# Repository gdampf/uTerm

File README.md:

## uTerm

uTerm (micro-Term) is a VT100-like terminal for the Z80-MBC2 (https://hackaday.io/project/159973). It has a VGA out and PS/2 keyboard connector, a power supply for the Z80-MBC2 and a "transparent" serial-USB port.

This fork of https://github.com/SuperFabius/uTerm was originally made for supporting German Keyboard-Layout.
Then, I recognized, that some kind of keyboards with PS/2 doesn't react at the given firmware. They are just sending out 0xAA all the time and no key codes. By comparing the signals to a system, where they are working fine, I found that they need a reset (0xff), to work propperly.
This fork solve therefore three things:

1. the state machine for the keyboard has been changed to support this kind of keyboards, which are waiting for reset.
2. the right alt key is now used as a separate modifier to support the ALTGR-Codes on many non US-Keyboard-Layouts.
3. the keys are changed corresponding to German Layout

To compile this code, I used Keil µVision5 under Windows X!

I further added the code for using an ESP8266 for using telnet via WiFi.

Here comes the original Text:

These are the sources modified for the uTerm forked from the Madis Kaal 
repository (forked from the original repository of K. C. Lee: 
https://github.com/FPGA-Computer/STM32F030F4-VGA. Original project 
page: https://hw-by-design.blogspot.com/2018/07/low-cost-vga-terminal-module-project.html)

uTerm "project" page: https://hackaday.io/project/165325

NOTE: I've updated here only the changed source files, so you must recompile all to get the new executable.

Supported uTerm boards:

- A071218-R250119
- A071218-R290319

Supported uTerm-S boards:

- A200419

------------------------------------------------------------------------------

**UPDATE (11/2019):** Solved a bug (by gkaufman) using the right CTRL key in some situations (i.e. CTRL-L)

------------------------------------------------------------------------------

In the following the original text. 

------------------------------------------------------------------------------
------------------------------------------------------------------------------

VT100 emulation, font editor, 16-line font, and support for inverse fonts
added by Madis Kaal <mast@nomad.ee> http://www.nomad.ee

The individual license(s) are in each directories.

Directories:
------------------------------------------------------------------------------
font conv/ 
- source code + Windows console executable for a font conversion program.
It imports GLCD font Creator file and converter it to a C font table
of the comverted scan line bitmaps that is to be used with the VGA library.

- The converter is compiled using Pelles C
http://www.pellesc.de/index.php?page=start&lang=en

- "GLCD Font Creator" MikroElektronika
http://www.mikroe.com/glcd-font-creator/

Code in this directory is licensed under "Simplified BSD License"

-------------------------------------------------------------------------------
STM32F030F4/Hardware/LT Spice Simulation
files in this directory is licensed under "Simplified BSD License"

-------------------------------------------------------------------------------
STM32F030F4/Hardware/Sketchup 3D Model
Creative Commons 4.0 Attribution-NonCommercial-NoDerivs International
http://creativecommons.org/licenses/by-nc-nd/4.0/

This is to prevent someone photoshopping this as their own project for crowd-funding 
scams. You are free to generate your own model using Eagleup from your new layout.

-------------------------------------------------------------------------------
STM32F030F4/Hardware/
Schematic/Layout is distributed with Creative Commons 4.0 Attribution-NonCommercial
http://creativecommons.org/licenses/by-nc/4.0/

If you want to sell this and want a different licensing term, please contact me.

-------------------------------------------------------------------------------
STM32F030F4/Firmware/

Source code distributed under GPLV3, with exception of fontedit.py that is
distributed under BSD license.

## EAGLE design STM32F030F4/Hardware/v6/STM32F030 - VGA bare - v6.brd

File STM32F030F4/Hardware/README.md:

ChibiTerm
---------
This is the repository for the Low Cost VGA Terminal Module PCB.

Licensing:
Schematic/Layout is distributed with Creative Commons 4.0 Attribution-NonCommercial

3D modelling: Creative Commons 4.0 Attribution-NonCommercial-NoDerivs International
This is to prevent someone photoshopping this as their own project for crowd-funding scams. You are allowed to generate your own model using Eagleup from your new layout.

Creative Commons 4.0 Attribution-NonCommercial:
See http://creativecommons.org/licenses/by-nc/4.0/

Creative Commons 4.0 Attribution-NonCommercial-NoDerivatives International
See http://creativecommons.org/licenses/by-nc-nd/4.0/

If you want to sell this and want a different licensing term, please contact me.

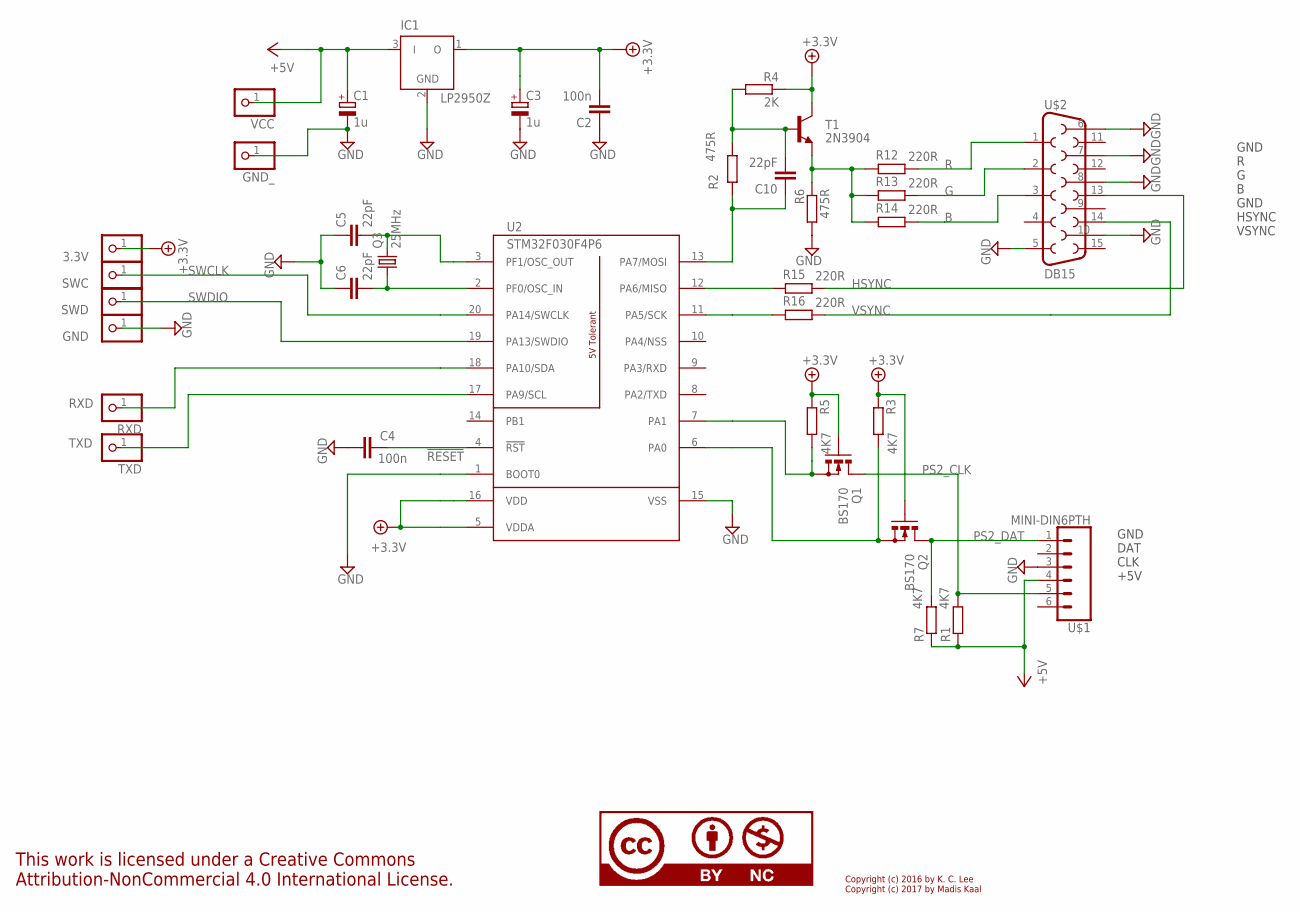
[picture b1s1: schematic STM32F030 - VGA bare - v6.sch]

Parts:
3.3V: PINHD-1X1; 1X01
C1, C3: 1u; E2,5-5
C2, C4: 100n; C025-025X050; PARTNO 0.1UF, 0603
C5, C6, C10: 22pF; C025-025X050; PARTNO 22PF, 0603
GND: PINHD-1X1; 1X01
GND_: PINHD-1X1; 1X01
IC1: LP2950Z; TO92
LICENSE: CC-BY-NC; CC-BY-NC-75; PARTNO LICENSE
Q1, Q2: BS170; SOT54E
Q3: 25MHz; HC49U-V
R1, R3, R5, R7: 4K7; 0204/7; PARTNO 4K7, 0603
R2, R6: 475R; 0204/7; PARTNO 475R, 0603
R4: 2K; 0204/7; PARTNO 2K, 0603
R12, R13, R14, R15, R16: 220R; 0204/7
RXD: PINHD-1X1; 1X01
SWC: PINHD-1X1; 1X01
SWD: PINHD-1X1; 1X01
T1: 2N3904; TO92
TXD: PINHD-1X1; 1X01
U2: STM32F030F4P6; TSSOP20; PARTNO STM32F030F4P6
U$1: MINI-DIN6PTH; MINI-DIN6
U$2: DB15
VCC: PINHD-1X1; 1X01

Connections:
!RESET: C4.1, U2.4 (!RST)
+3.3V: 3.3V.1, C2.2, C3.+, IC1.1 (O), Q1.G, Q2.G, R3.2, R4.1, R5.2, T1.1 (C), U2.5 (VDDA), U2.16 (VDD)
+5V: C1.+, IC1.3 (I), R1.2, R7.2, U$1.4, VCC.1
B: R14.1, U$2.3
G: R13.1, U$2.2
GND: C1.-, C2.1, C3.-, C4.2, C5.1, C6.1, GND.1, GND_.1, IC1.2 (GND), R6.2, U2.1 (BOOT0), U2.15 (VSS), U$1.3, U$2.5, U$2.6, U$2.7, U$2.8, U$2.10
HSYNC: R15.1, U$2.13
unnamed: R6.1, R12.2, R13.2, R14.2, T1.3 (E)
unnamed: R15.2, U2.12 (PA6/MISO)
unnamed: Q1.S, R5.1, U2.7 (PA1)
unnamed: C5.2, Q3.2, U2.3 (PF1/OSC_OUT)
unnamed: C6.2, Q3.1, U2.2 (PF0/OSC_IN)
unnamed: Q2.S, R3.1, U2.6 (PA0)
unnamed: R16.2, U2.11 (PA5/SCK)
unnamed: C10.2, R2.1, R4.2, T1.2 (B)
unnamed: C10.1, R2.2, U2.13 (PA7/MOSI)
PS2_CLK: Q1.D, R1.1, U$1.5
PS2_DAT: Q2.D, R7.1, U$1.1
R: R12.1, U$2.1
RXD: RXD.1, U2.18 (PA10/SDA)
SWCLK: SWC.1, U2.20 (PA14/SWCLK)
SWDIO: SWD.1, U2.19 (PA13/SWDIO)
TXD: TXD.1, U2.17 (PA9/SCL)
VSYNC: R16.1, U$2.14

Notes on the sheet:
GND R G B GND HSYNC VSYNC
GND DAT CLK +5V
Copyright (c) 2016 by K. C. Lee Copyright (c) 2017 by Madis Kaal

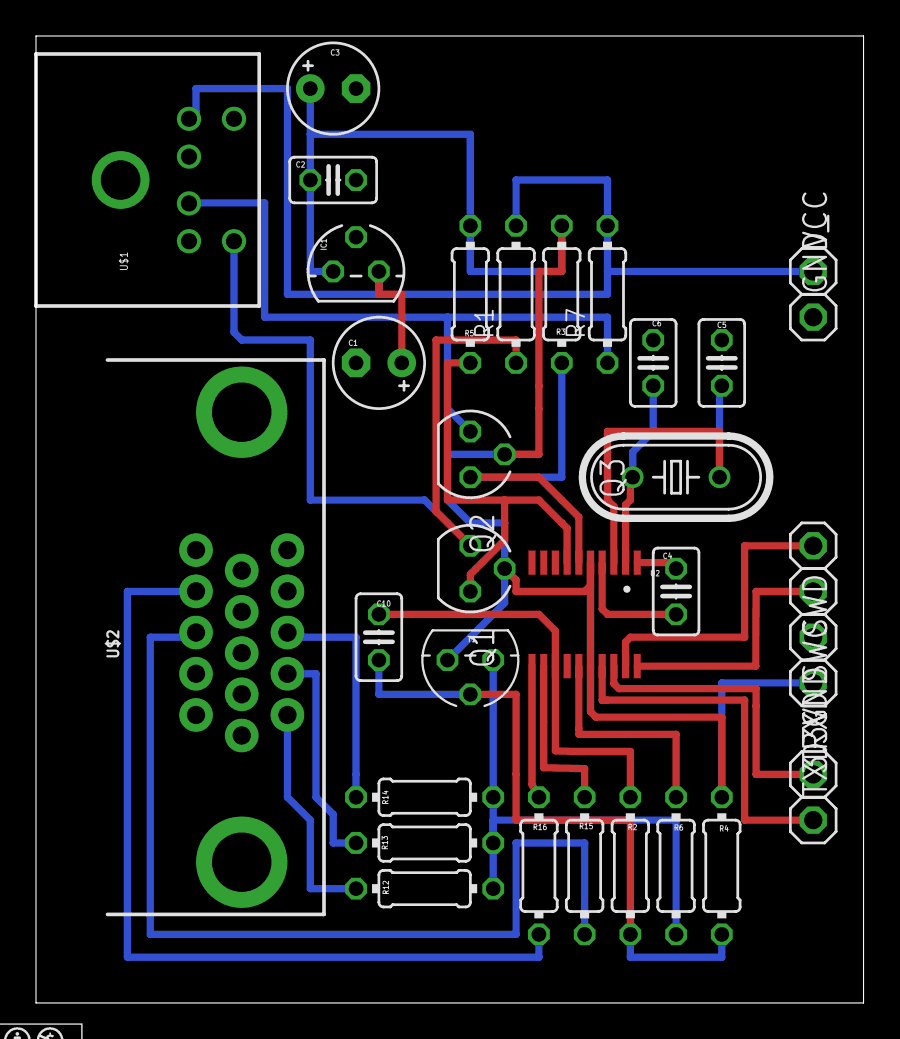
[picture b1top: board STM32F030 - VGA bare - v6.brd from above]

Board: 2 copper layers, 46.0 x 53.7 mm, 36 parts (0 on the bottom side), 24 nets.

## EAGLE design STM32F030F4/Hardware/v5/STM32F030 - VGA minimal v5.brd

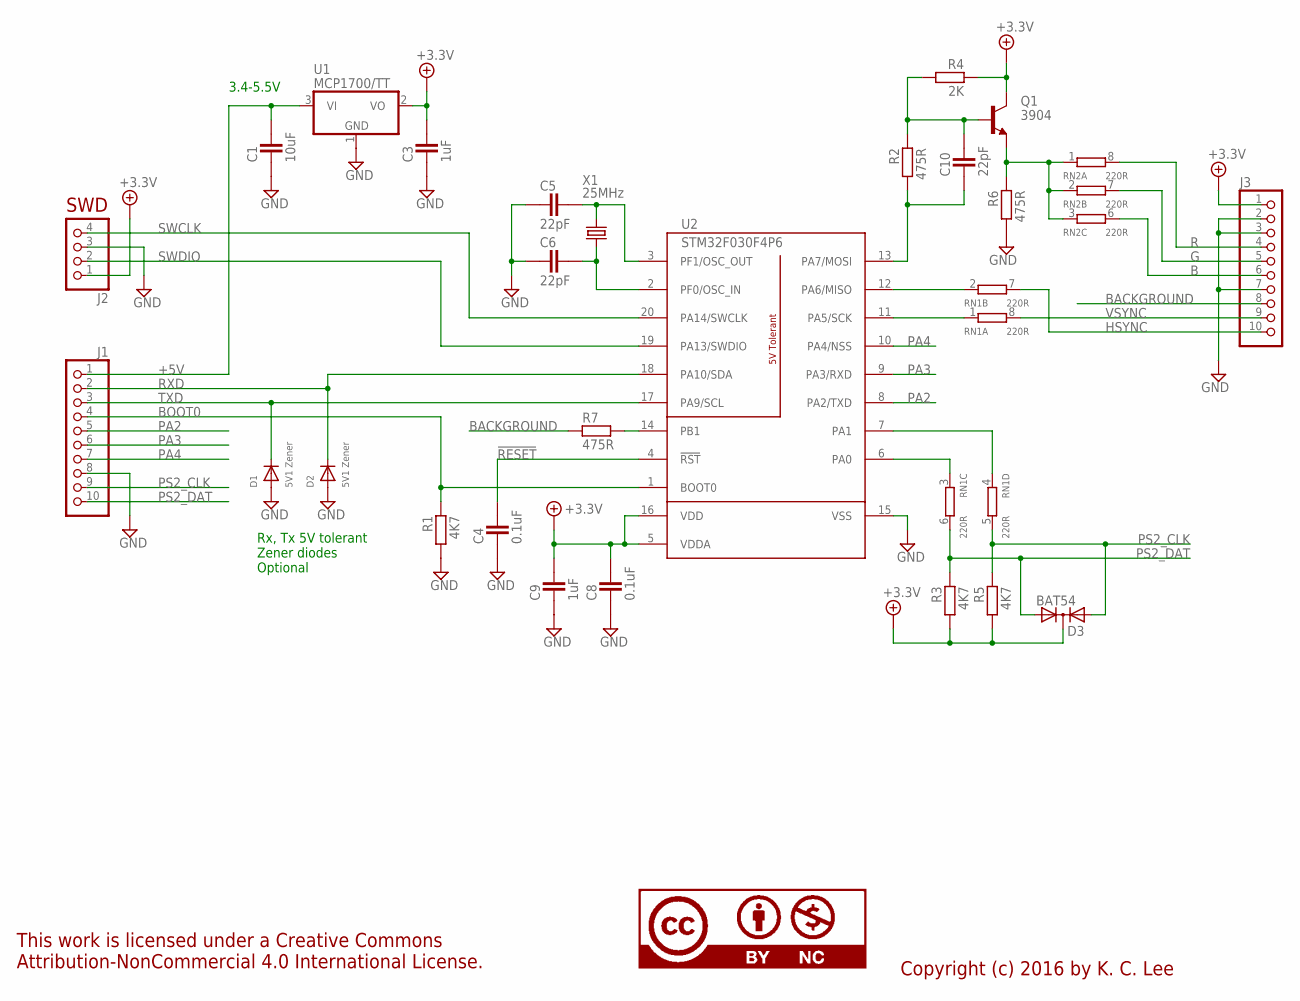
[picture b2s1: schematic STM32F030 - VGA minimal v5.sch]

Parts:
C1: 10uF; CAPC2012X145AN; PARTNO 10UF/10V X5R 0805
C3: 1uF; CAPC2012X145AN; PARTNO 1UF, 0805
C4, C8: 0.1uF; CAPC1608X92N; PARTNO 0.1UF, 0603
C5, C6, C10: 22pF; CAPC1608X92N; PARTNO 22PF, 0603
C9: 1uF; CAPC1608X92N; PARTNO 1UF, 0603
D1, D2: 5V1 Zener; SOD-123; PARTNO BZT52C5V1
D3: BAT54; SOT95P280X135-3N; PARTNO BAT54
J1, J3: PINHD-1X10; 1X10; PARTNO 0.1 IN HEADER 1X10
J2: PINHD-1X4_2.54; 1X04; PARTNO 0.1 IN HEADER 1X4
LICENSE: CC-BY-NC; CC-BY-NC-75; PARTNO LICENSE
Q1: 3904; SOT95P280X135-3N; PARTNO MMBT3904
R1, R3, R5: 4K7; RESC1608X55N; PARTNO 4K7, 0603
R2, R6, R7: 475R; RESC1608X55N; PARTNO 475R, 0603
R4: 2K; RESC1608X55N; PARTNO 2K, 0603
RN1, RN2: 220R; CAT16; PARTNO CAT16-221J4
U1: MCP1700/TT; SOT95P280X135-3N; PARTNO MCP1700T-3302E/TT
U2: STM32F030F4P6; TSSOP20; PARTNO STM32F030F4P6
X1: 25MHz; SM49; PARTNO 25MHZ FUND. HC49

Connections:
!RESET: C4.2, U2.4 (!RST)
+3.3V: C3.2, C8.2, C9.2, D3.3 (K), J2.1, J3.1, Q1.3 (C), R3.2, R4.1, R5.2, U1.2 (VO), U2.5 (VDDA), U2.16 (VDD)
+5V: C1.2, J1.1, U1.3 (VI)
B: J3.6, RN2.6 (2)
BACKGROUND: J3.8, R7.1
BOOT0: J1.4, R1.1, U2.1 (BOOT0)
G: J3.5, RN2.7 (2)
GND: C1.1, C3.1, C4.1, C5.1, C6.1, C8.1, C9.1, D1.A, D2.A, J1.8, J2.3, J3.2, J3.3, J3.7, R1.2, R6.2, U1.1 (GND), U2.15 (VSS)
HSYNC: J3.10, RN1.7 (2)
unnamed: Q1.2 (E), R6.1, RN2.1, RN2.2 (1), RN2.3 (1)
unnamed: RN1.2 (1), U2.12 (PA6/MISO)
unnamed: RN1.4 (1), U2.7 (PA1)
unnamed: R7.2, U2.14 (PB1)
unnamed: C5.2, U2.3 (PF1/OSC_OUT), X1.2
unnamed: C6.2, U2.2 (PF0/OSC_IN), X1.1
unnamed: RN1.1, U2.11 (PA5/SCK)
unnamed: RN1.3 (1), U2.6 (PA0)
unnamed: C10.2, Q1.1 (B), R2.1, R4.2
unnamed: C10.1, R2.2, U2.13 (PA7/MOSI)
PA2: J1.5, U2.8 (PA2/TXD)
PA3: J1.6, U2.9 (PA3/RXD)
PA4: J1.7, U2.10 (PA4/NSS)
PS2_CLK: D3.2 (A2), J1.9, R5.1, RN1.5 (2)
PS2_DAT: D3.1 (A1), J1.10, R3.1, RN1.6 (2)
R: J3.4, RN2.8 (2)
RXD: D2.C, J1.2, U2.18 (PA10/SDA)
SWCLK: J2.4, U2.20 (PA14/SWCLK)
SWDIO: J2.2, U2.19 (PA13/SWDIO)
TXD: D1.C, J1.3, U2.17 (PA9/SCL)
VSYNC: J3.9, RN1.8 (2)

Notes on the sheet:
3.4-5.5V
Rx, Tx 5V tolerant Zener diodes Optional
Copyright (c) 2016 by K. C. Lee
SWD

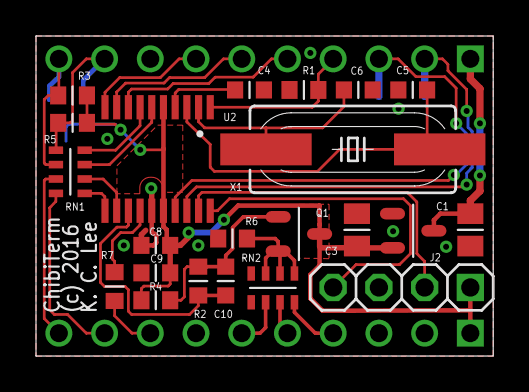
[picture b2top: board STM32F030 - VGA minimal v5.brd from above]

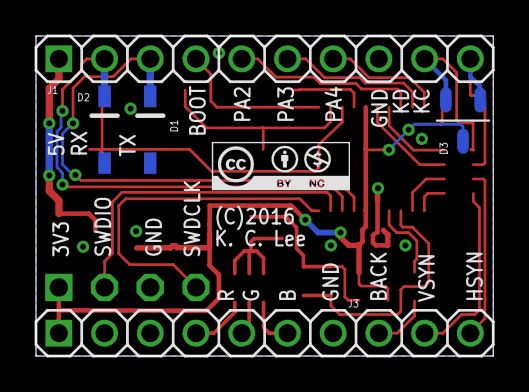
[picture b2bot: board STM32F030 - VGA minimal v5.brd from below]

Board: 2 copper layers, 25.4 x 17.8 mm, 28 parts (6 on the bottom side), 30 nets.

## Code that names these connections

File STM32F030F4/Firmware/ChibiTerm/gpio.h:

/*
 * gpio.h
 *
 * Created: March-12-16, 5:37:11 PM
 *  Author: K. C. Lee
 * Copyright (c) 2016 by K. C. Lee 
 
 	This program is free software: you can redistribute it and/or modify
	it under the terms of the GNU General Public License as published by
	the Free Software Foundation, either version 3 of the License, or
	(at your option) any later version.

	This program is distributed in the hope that it will be useful,
	but WITHOUT ANY WARRANTY; without even the implied warranty of
	MERCHANTABILITY or FITNESS FOR A PARTICULAR PURPOSE.  See the
	GNU General Public License for more details.

	You should have received a copy of the GNU General Public License
	along with this program.

	If not, see http://www.gnu.org/licenses/gpl-3.0.en.html
 */ 

#ifndef _GPIO_H_
#define _GPIO_H_

// STM32F030F4 GPIO

enum GPIO_A_PINS
{ 
	PA0,PA1,PA2,PA3,PA4,PA5,PA6,PA7,
  PA9=9,PA10=10,PA13=13,PA14=14
};

enum GPIO_B_PINS
{	
	PB1=1
};

enum GPIO_F_PINS
{
	PF0,PF1
};

#define PIN_F2(BIT,FUNC) 		((FUNC)<<(BIT*2))

// MODER
#define PIN_ANALOG(BIT)				PIN_F2(BIT,0x03)
#define PIN_INPUT(BIT)				PIN_F2(BIT,0x00)
#define PIN_OUTPUT(BIT)				PIN_F2(BIT,0x01)
#define PIN_ALT(BIT)					PIN_F2(BIT,0x02)

// AFR[0]
#define PIN_AFRL(BIT,AF)			(AF<<((BIT)*4))
// AFR[1]
#define PIN_AFRH(BIT,AF)			PIN_AFRL(BIT-8,AF)

// OSPEEDR
#define PIN_OSPEED(BIT,SPEED) PIN_F2(BIT,SPEED)

// OTYPER
#define PIN_PUSHPULL(BIT)			0
#define PIN_OPENDRAIN(BIT)		(1<<BIT)

// PUPDR
#define PIN_PULLUP(BIT)				PIN_F2(BIT,0x01)
#define PIN_PULLDOWN(BIT)			PIN_F2(BIT,0x02)

// BSRR
#define PIN_SET(BIT)					(1<<BIT)
#define PIN_CLR(BIT)					(1<<(BIT+16))
#endif

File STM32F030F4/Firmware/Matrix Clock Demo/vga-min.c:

/*
 * vga-min.c
 *
 * Created: March-16-2016, 3:50:27 PM
 *  Author: K. C. Lee
 * Copyright (c) 2016 by K. C. Lee
 
	This program is free software: you can redistribute it and/or modify
	it under the terms of the GNU General Public License as published by
	the Free Software Foundation, either version 3 of the License, or
	(at your option) any later version.

	This program is distributed in the hope that it will be useful,
	but WITHOUT ANY WARRANTY; without even the implied warranty of
	MERCHANTABILITY or FITNESS FOR A PARTICULAR PURPOSE.  See the
	GNU General Public License for more details.

	You should have received a copy of the GNU General Public License
	along with this program.

	If not, see http://www.gnu.org/licenses/gpl-3.0.en.html 
 */ 

#include "vga-min.h"
#include "vga font.h"

__align(4) uint8_t TextBuffer[VGA_TEXT_X*VGA_TEXT_Y];
__align(4) uint8_t ScanLineBuf[SPI_BUF_SIZE*2+1];

uint16_t VGA_Line;					// current VGA line
uint8_t  Display_Flags;

volatile uint16_t MicroTimer0;
void (* VerticalBlank)(void);

#define ScanLine_Buf0		&ScanLineBuf[0]
#define ScanLine_Buf1		&ScanLineBuf[SPI_BUF_SIZE+1]

void VGA_Init(void)
{
	// GPIO default: input
	// PA13, PA14 = SWD
	
	// Enable GPIO and DMA clock
	RCC->AHBENR |= RCC_AHBENR_GPIOAEN|RCC_AHBENR_GPIOBEN|RCC_AHBENR_GPIOFEN|RCC_AHBENR_DMAEN;
	// Enable SPI, UART1 clock
  RCC->APB2ENR |= RCC_APB2ENR_SPI1EN|RCC_APB2ENR_USART1EN|							// Enable SPI, UART, SYSCFG
	                RCC_APB2ENR_SYSCFGCOMPEN;
	// Enable TIM3
	RCC->APB1ENR |= RCC_APB1ENR_TIM3EN;
	
  // Select pin types
	GPIOA->MODER = GPIOA_MODER|PIN_ALT(PA7)|PIN_ALT(PA6)|PIN_OUTPUT(PA5); // MOSI, VSync, HSync
	GPIOA->AFR[0] = PIN_AFRL(PA7,0)|PIN_AFRL(PA6,1);											// MOSI,TIM3 CH1

	GPIOA->OTYPER = GPIOA_OTYPER;
	GPIOA->BSRR = GPIOA_BSRR;	
	GPIOA->AFR[1] = GPIOA_AFR1;
	
	// SPI: (SCK, MOSI) slew rate = 11 (fastest)
  // Don't seems to have an effect on the video quality.  Use default for EMI control
	
// GPIOA->OSPEEDR = PIN_OSPEED(PA7,GPIO_OSPEEDR_OSPEEDR0_1|GPIO_OSPEEDR_OSPEEDR0_1)|
//	                 PIN_OSPEED(PA5,GPIO_OSPEEDR_OSPEEDR0_1|GPIO_OSPEEDR_OSPEEDR0_1);

#ifdef DMA_SPI_TIMING_TWEAK
  GPIOB->MODER  = PIN_ALT(PB1);																			// TIM3 CH4 (Display enable)
	GPIOB->AFR[0] = PIN_AFRL(PB1,1);																	// TIM3 CH4
#else	
	GPIOB->MODER  = PIN_OUTPUT(PB1);
#endif	
	
  GPIOF->MODER  = PIN_OUTPUT(PF1)|PIN_INPUT(PF0);
  // TIM3 CH4 slew rate = 11 (fastest)
	GPIOB->OSPEEDR = PIN_OSPEED(PB1,GPIO_OSPEEDR_OSPEEDR0_1|GPIO_OSPEEDR_OSPEEDR0_1);
		
/*
         0                                  VGA_PIX_X
 				       _______________________________
  HSync   ____/                               \			  TIM3 C1: VGA_HSYNC
																															 
	SPI DMA   |																					TIM3 C2: tweak for IRQ latency for TIM1 C3	
          ______ _______________________________
	Display ______X_______________________________ 			TIM3 C4: VGA_HSYNC+VGA_HSYNC_BP+VGA_BORDER_LEFT

*/
	VGA_Line = 0;
	
	// TIM3 CH1: HSync
  TIM3->CCR1 =  VGA_HSYNC_CNT;																					// set rising edge
  TIM3->CCMR1 = TIM_CCMR1_OC1M_2|TIM_CCMR1_OC1M_1|TIM_CCMR1_OC1PE;			// OC1 PWM1, preload																					
								
	// TIM3 CH2 -> IRQ -> SPI DMA 3
  TIM3->CCR2 = VGA_DMA_START;
	
#ifdef DMA_SPI_TIMING_TWEAK
	// TIM3 CH4 -> Display Enable (tweaking only)
	TIM3->CCR4 = VGA_DISPLAY_ON;
  TIM3->CCMR2 = TIM_CCMR2_OC4M_1|TIM_CCMR2_OC4M_0|TIM_CCMR2_OC4PE;			// OC4 toggle on match
  TIM3->CCER = TIM_CCER_CC1E|TIM_CCER_CC1P|TIM_CCER_CC4E; 							// OC1, OC2, OC4 enabled
#else
  TIM3->CCER = TIM_CCER_CC1E|TIM_CCER_CC1P; 														// OC1, OC2 enabled
#endif

	// TIM1 Init
	TIM3->PSC = TIM3_PRESCALER;																						// prescaler = pclk/2
  TIM3->ARR = VGA_DOTS_CNT;																							// timer reload = # of pixels per line
	TIM3->DIER |= TIM_DIER_UIE|TIM_DIER_CC2IE;														// TIM1 update interrupt, CC3 DMA, CC4 IRQ
	TIM3->EGR |= TIM_EGR_UG;	
	TIM3->BDTR |= TIM_BDTR_MOE;																						// Main output enable
  TIM3->CR1 |= TIM_CR1_CEN|TIM_CR1_URS;						 			 								// enable TIM, under/over flow updates only
									 	
  // SPI init
	SPI1->CR1 = SPI_CR1_MSTR|SPI_CR1_SSM|SPI_CR1_SSI|SPI_CR1_EXTRA; 			// Master, BR: Fpclk/2
	SPI1->CR2 = SPI_CR2_DATASIZE|SPI_CR2_TXDMAEN|SPI_CR2_EXTRA;						// set Data Size, SPI TX DMA enable 
																																				// TI mode: MOSI idle at 0.
	SPI1->CR1 |= SPI_CR1_SPE;

  // DMA Ch3 - SPI
	DMA1_Channel3->CPAR = (uint32_t) &SPI1->DR;

  // NVIC IRQ
  NVIC_SetPriority(TIM3_IRQn,TIM3_IRQ_PRIORITY);												// Highest priority
  NVIC_EnableIRQ(TIM3_IRQn);
	
	NVIC_SetPriority(PendSV_IRQn,PENDSV_PRIORITY);
	NVIC_EnableIRQ(PendSV_IRQn);
}

void TIM3_IRQHandler(void)
{
	if(TIM3->SR & TIM_SR_CC2IF)
	{
		DMA1_Channel3->CCR = DMA_CCR_PL_1|DMA_CCR_PL_0|DMA_CCR_MINC|				// Very high priority, memory increment
												 DMA_CCR_DIR|SPI_DMA_CCR_SIZE|DMA_CCR_EN;				// trigger DMA transfer

		if(Display_Flags & VGA_RENDER)																			// render loop
		{ 
			uint8_t i,*textbuf,*scanline,*font;
			uint16_t line = VGA_Line-(VGA_DISPLAY_START-1);
			
	    scanline = (Display_Flags & VGA_BUFFER)?ScanLine_Buf0+1:ScanLine_Buf1+1;			
	    font = (uint8_t *) &FONT_TABLE[line%FONT_ROW];			
			textbuf = &TEXT_BUF(0,line/FONT_ROW);

	    for(i=0;i<VGA_TEXT_X/2;i++)
		  {
	      *scanline++ = font[(*textbuf++)*FONT_ROW];
			  *scanline++ = font[(*textbuf++)*FONT_ROW];
		  }	
		}
		TIM3->SR &= ~TIM_SR_CC2IF;
	}
  else if(TIM3->SR & TIM_SR_UIF)
	{
	  VGA_Line++;
		
		switch(VGA_Line)
    {
			case VGA_VSYNC_START:
#ifdef VSYNC 
				VSYNC_ASSERT();																	// Set VSync
#else									
	      TIM3->CCER &= ~TIM_CCER_CC1P;										// CSync: flip polarity
#endif
				break;
			
			case VGA_VSYNC_STOP:							
#ifdef VSYNC 				
        VSYNC_DEASSERT();																// Reset VSync
#else
	      TIM3->CCER |= TIM_CCER_CC1P;
#endif			
				break;

			case VGA_DISPLAY_START-1:		
				Display_Flags = VGA_RENDER|VGA_BUFFER0;
				break;			

			case VGA_DISPLAY_START:	
				Display_Flags |= VGA_DISPLAY;
				break;						
			
			case VGA_DISPLAY_STOP-1:
			  Display_Flags &= ~VGA_RENDER;
			  break;
			
			case VGA_DISPLAY_STOP:
				Display_Flags = 0;
			  break;
			
			case VGA_LINES:																			// Reach bottom of display
				VGA_Line=0;
			
			  if (VerticalBlank)																// Callback code
			    (* VerticalBlank)();
				break;
			}
		
		if(Display_Flags)
		{
      if(Display_Flags & VGA_DISPLAY)
			{
				DMA1_Channel3->CCR &= ~DMA_CCR_EN;
				DMA1_Channel3->CNDTR = SPI_DMA_WORDS;							// # of transfers					
				DMA1_Channel3->CMAR = (uint32_t)((Display_Flags&VGA_BUFFER)?ScanLine_Buf0:ScanLine_Buf1);
				
				// Set PendAV
				SCB->ICSR |= SCB_ICSR_PENDSVSET_Msk;
			}
			
			Display_Flags ^= VGA_BUFFER;
		}
		
		if (MicroTimer0) 
		  MicroTimer0--;
					
		TIM3->SR = ~TIM_SR_UIF;																// clear interrupt flag
	}
}

// Put ARM core to sleep and wait for TIM3 OC2 IRQ to wake it up.
void PendSV_Handler(void)
{
	NVIC_DisableIRQ(USART1_IRQn);
  NVIC_DisableIRQ(EXTI0_1_IRQn);
	
	// Clear pendSV flag
	SCB->ICSR |= SCB_ICSR_PENDSVCLR_Msk;
	
	__WFI();		// Sleep here
	
	NVIC_EnableIRQ(USART1_IRQn);
	NVIC_EnableIRQ(EXTI0_1_IRQn);	
 }

// Time delay in 32us ticks - Hsync
void Delay(uint16_t Ticks)
{
	MicroTimer0 = Ticks;
	
	while(MicroTimer0)
		/* Busy wait */;
}

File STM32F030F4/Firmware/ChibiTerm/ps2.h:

/*
 * ps2.h
 *
 * Created: March-11-16, 5:51:16 PM
 *  Author: K. C. Lee
 * Copyright (c) 2016 by K. C. Lee 
 
 	This program is free software: you can redistribute it and/or modify
	it under the terms of the GNU General Public License as published by
	the Free Software Foundation, either version 3 of the License, or
	(at your option) any later version.

	This program is distributed in the hope that it will be useful,
	but WITHOUT ANY WARRANTY; without even the implied warranty of
	MERCHANTABILITY or FITNESS FOR A PARTICULAR PURPOSE.  See the
	GNU General Public License for more details.

	You should have received a copy of the GNU General Public License
	along with this program.

	If not, see http://www.gnu.org/licenses/gpl-3.0.en.html
 */

#ifndef _PS2_H_
#define _PS2_H_

#include <stdio.h>
#include <stdint.h>
#include "stm32f0xx.h"
#include "system_stm32f0xx.h"
#include "gpio.h"
#include "fifo.h"
#include "vga-min.h"

#define PS2_RX_DEBUG

#define PS2_IRQ_PRIORITY  			3
#define PS2_FIFO_Size						4

#define PS2_PORT								GPIOA
#define PS2_CLK									PA1
#define PS2_DAT									PA0

#define PS2_CLK_BIT							(1<<PS2_CLK)
#define PS2_DAT_BIT							(1<<PS2_DAT)

void    	PS2_Init(void);
int16_t 	PS2_Get(void);
uint8_t 	PS2_Send(uint8_t Cmd);
void 			PS2_Task(void);
uint16_t 	PS2_Parity(uint8_t byte);
void    	PS2_Decode(uint8_t key_code);
void      NumLockOn(void);
void      NumLockOff(void);

extern  	FIFO_Data_t PS2_Buf[];

typedef union
{
	uint16_t		Init;
	struct
	{
		uint16_t	Code:11;
		uint8_t 	BitCnt:4;
		uint8_t		WriteMode:1;
	} States;
} PS2_IF_t;


typedef struct 
{
  uint8_t State:2;
  uint8_t PrevKey:2;	
} PS2_State_t;

enum PS2_States 
{ 
  PS2_UNKNOWN, PS2_KBD_RDY, PS2_CMD, PS2_CMD_ACK
};

#define PREV_MODKEY(X)					(X-KEY_MODIFERS+1)

//#define PS2_RX_DEBUG

#define PS2_WRITE_MASK          0x80
#define PS2_RX_BITS             11
#define PS2_TX_BITS             12

#define PS2_START_BIT           (1<<0)
#define PS2_PARITY_BIT         	(1<<9)
#define PS2_STOP_BIT           	(1<<10)
#define PS2_ACK_BIT            	(1<<11)

#define PS2_BIT_TIMEOUT					275			// Toshiba keyboard last 2 bits are slow
#define PS2_BUSY_WAIT_us        200
#define PS2_CMD_START_us        125
#define PS2_TIMEOUT             255

// Common PS2 command
#define PS2_GET_DEVICEID        0xf2
#define PS2_CMD_RESEND          0xfe
#define PS2_CMD_RESET           0xff

// Common PS/2 response
#define PS2_RESPOND_INIT_OK     0xaa
#define PS2_RESPOND_ACK         0xfa
#define PS2_RESPOND_RESEND      0xfe
#define PS2_RESPOND_FAIL        0xfc
#define PS2_RESPOND_FAIL2       0xfd
#define PS2_RESPOND_MS_ID       0x00 // some docs say keyboard error
																		 // in modes 2 and 3

// pseudo keyboard code return for garbled data
#define PS2_KBD_ERR_CODE				0xff

// Keyboard Modifier/LED
#define PS2_KBD_CMD_LED         0xed
#define PS2_KBD_LED_MASK        0x07
#define PS2_KBD_LED_SCROLL      0x01
#define PS2_KBD_LED_NUM         0x02
#define PS2_KBD_LED_CAPS        0x04

#define PS2_MOD_SCROLL					PS2_KBD_LED_SCROLL
#define PS2_MOD_NUM							PS2_KBD_LED_NUM
#define PS2_MOD_CAPS						PS2_KBD_LED_CAPS

#define PS2_KBD_CODE_EXTENDED   0xe0
#define PS2_KBD_CODE_RELEASE    0xf0

/*
#define PS2_KBD_TYPEMATIC       0xf3
#define PS2_KBD_MF2_ID1         0xab
#define PS2_KBD_MF2_ID2         0x83
*/


#endif

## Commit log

2016-03-16 added options for font conv
2016-03-21 PCB Rev 1 release
2016-03-21 fix readme.md
2016-03-21 PCB Rev 1 add BOM
2016-03-21 PCB Rev 1 - fix BOM
2016-03-21 PCB Rev 1 - fix BOM take 2
2016-03-21 PCB Rev 1 - fix BOM take 3
2016-03-21 PCB Rev 1 - fix BOM take 4
2016-03-21 PCB Rev 1 - fix BOM take 5
2016-03-21 PCB Rev 1 - fix BOM take 6
2016-03-21 Add Matrix Clock Demo
2016-03-21 change readme.md
2016-03-21 More readme edits
2016-03-22 Use DDS for time
2016-03-22 remove backup
2016-04-18 ChibiTerm source snapshot
2016-04-18 ChibiTerm source snapshot - cleanup
2016-04-18 ChibiTerm source snapshot take 3
2016-04-18 ChibiTerm source snapshot take 4
2016-04-18 V5 Schematic/layout/3D model
2016-04-19 Zener diodes value change
2016-04-19 Cleanup
2016-04-25 VGA pin 9 is a RES/PWR. :(
2016-04-29 Fix silly typo/bug
2017-10-24 VT100 emulation added
2017-10-24 Updated readme's and release notes
2019-05-06 Changes for the uTerm (A071218)
2019-05-06 Changes for uTerm
2019-12-01 Solved bug with right CTRL key
2021-04-20 New binaries
    enhanced Protocoll, ALTGR, German Keyboard Layout
2021-04-20 Delete STM32F030F4/Firmware/ChibiTerm/Listings directory
    Deleting Listings (no value)
2021-04-20 enhanced PS/2
    to support more keyboards, ALTGR and German Layout
2021-04-20 Update README.md
    correct Typos
2021-04-20 Telnet via WiFi
    Nice little add on to µTerm: Telnet via WiFi
2021-04-20 modified sketch for arduino
    This sketch is modified to allow OTA updates, but originally based on the code found here: http://blog.thesen.eu
    See picture for usage. The wiring is just trivial, as you just have to connect TxD, RxD, Vcc, Gnd and some protecting resistors.
    Buttons are for reset and wired programming only.

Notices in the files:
parts and their libraries:
Misc logo: This work is licensed under a Creative Commons
Attribution-NonCommercial 4.0 International License.
SparkFun-Retired: Licensing: Creative Commons ShareAlike 4.0 International - https://creativecommons.org/licenses/by-sa/4.0
